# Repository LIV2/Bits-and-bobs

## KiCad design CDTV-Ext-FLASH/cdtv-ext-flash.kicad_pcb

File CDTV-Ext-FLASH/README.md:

# CDTV Extended rom adapter for 39SF010/020/040

## License

[![CC BY-SA 4.0][cc-by-sa-shield]][cc-by-sa]

This work is licensed under a
[Creative Commons Attribution-ShareAlike 4.0 International License][cc-by-sa].

[![CC BY-SA 4.0][cc-by-sa-image]][cc-by-sa]

[cc-by-sa]: http://creativecommons.org/licenses/by-sa/4.0/
[cc-by-sa-image]: https://licensebuttons.net/l/by-sa/4.0/88x31.png
[cc-by-sa-shield]: https://img.shields.io/badge/License-CC%20BY--SA%204.0-lightgrey.svg

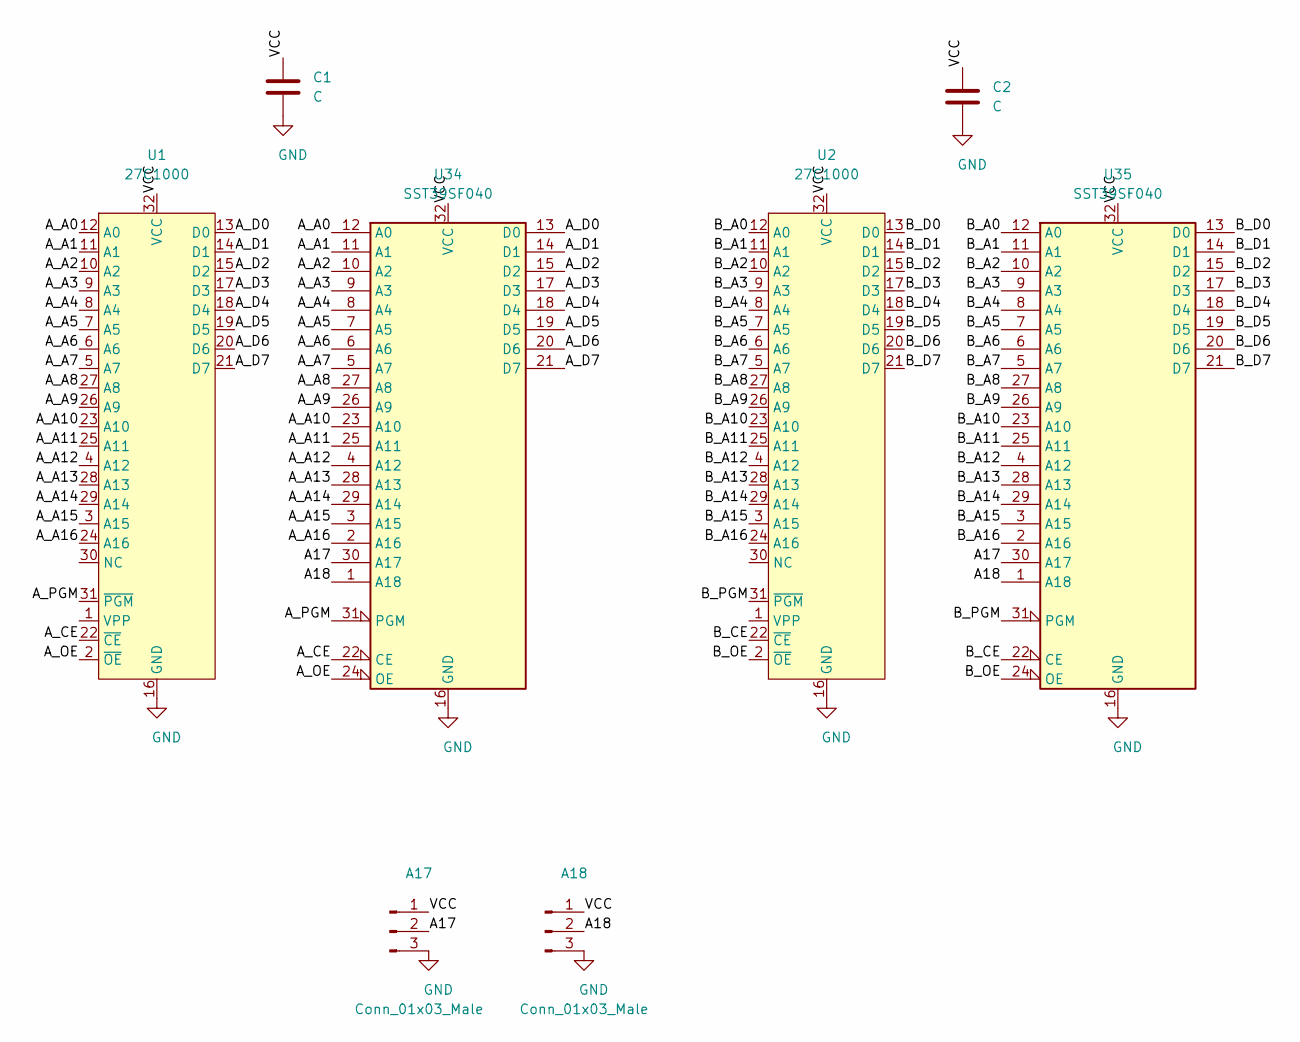
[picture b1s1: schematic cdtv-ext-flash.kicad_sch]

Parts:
A17, A18: Conn_01x03_Male; PinHeader_1x03_P2.54mm_Vertical
C1, C2: C; C_0805_2012Metric_Pad1.18x1.45mm_HandSolder
U1, U2: 27C1000; DIP-32_W15.24mm
U34, U35: SST39SF040; DIP-32_W15.24mm_Socket

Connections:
/A17: A17.2, U34.30 (A17), U35.30 (A17)
/A18: A18.2, U34.1 (A18), U35.1 (A18)
/A_A0: U1.12 (A0), U34.12 (A0)
/A_A1: U1.11 (A1), U34.11 (A1)
/A_A2: U1.10 (A2), U34.10 (A2)
/A_A3: U1.9 (A3), U34.9 (A3)
/A_A4: U1.8 (A4), U34.8 (A4)
/A_A5: U1.7 (A5), U34.7 (A5)
/A_A6: U1.6 (A6), U34.6 (A6)
/A_A7: U1.5 (A7), U34.5 (A7)
/A_A8: U1.27 (A8), U34.27 (A8)
/A_A9: U1.26 (A9), U34.26 (A9)
/A_A10: U1.23 (A10), U34.23 (A10)
/A_A11: U1.25 (A11), U34.25 (A11)
/A_A12: U1.4 (A12), U34.4 (A12)
/A_A13: U1.28 (A13), U34.28 (A13)
/A_A14: U1.29 (A14), U34.29 (A14)
/A_A15: U1.3 (A15), U34.3 (A15)
/A_A16: U1.24 (A16), U34.2 (A16)
/A_CE: U1.22 (~CE), U34.22 (CE)
/A_D0: U1.13 (D0), U34.13 (D0)
/A_D1: U1.14 (D1), U34.14 (D1)
/A_D2: U1.15 (D2), U34.15 (D2)
/A_D3: U1.17 (D3), U34.17 (D3)
/A_D4: U1.18 (D4), U34.18 (D4)
/A_D5: U1.19 (D5), U34.19 (D5)
/A_D6: U1.20 (D6), U34.20 (D6)
/A_D7: U1.21 (D7), U34.21 (D7)
/A_OE: U1.2 (~OE), U34.24 (OE)
/A_PGM: U1.31 (~PGM), U34.31 (PGM)
/B_A0: U2.12 (A0), U35.12 (A0)
/B_A1: U2.11 (A1), U35.11 (A1)
/B_A2: U2.10 (A2), U35.10 (A2)
/B_A3: U2.9 (A3), U35.9 (A3)
/B_A4: U2.8 (A4), U35.8 (A4)
/B_A5: U2.7 (A5), U35.7 (A5)
/B_A6: U2.6 (A6), U35.6 (A6)
/B_A7: U2.5 (A7), U35.5 (A7)
/B_A8: U2.27 (A8), U35.27 (A8)
/B_A9: U2.26 (A9), U35.26 (A9)
/B_A10: U2.23 (A10), U35.23 (A10)
/B_A11: U2.25 (A11), U35.25 (A11)
/B_A12: U2.4 (A12), U35.4 (A12)
/B_A13: U2.28 (A13), U35.28 (A13)
/B_A14: U2.29 (A14), U35.29 (A14)
/B_A15: U2.3 (A15), U35.3 (A15)
/B_A16: U2.24 (A16), U35.2 (A16)
/B_CE: U2.22 (~CE), U35.22 (CE)
/B_D0: U2.13 (D0), U35.13 (D0)
/B_D1: U2.14 (D1), U35.14 (D1)
/B_D2: U2.15 (D2), U35.15 (D2)
/B_D3: U2.17 (D3), U35.17 (D3)
/B_D4: U2.18 (D4), U35.18 (D4)
/B_D5: U2.19 (D5), U35.19 (D5)
/B_D6: U2.20 (D6), U35.20 (D6)
/B_D7: U2.21 (D7), U35.21 (D7)
/B_OE: U2.2 (~OE), U35.24 (OE)
/B_PGM: U2.31 (~PGM), U35.31 (PGM)
/VCC: A17.1, A18.1, C1.1, C2.1, U1.32 (VCC), U2.32 (VCC), U34.32 (VCC), U35.32 (VCC)
GND: A17.3, A18.3, C1.2, C2.2, U1.16 (GND), U2.16 (GND), U34.16 (GND), U35.16 (GND)

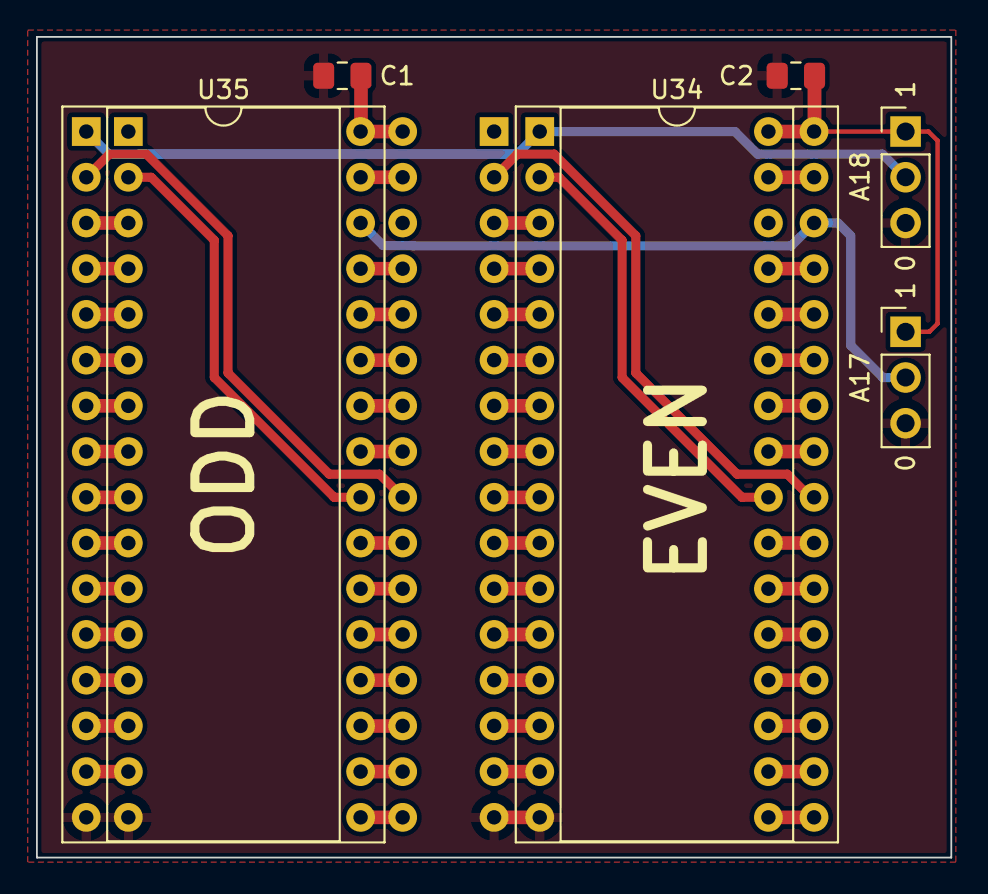
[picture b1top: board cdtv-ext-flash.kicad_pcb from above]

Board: 2 copper layers, 50.8 x 45.6 mm, 8 parts (0 on the bottom side), 60 nets.

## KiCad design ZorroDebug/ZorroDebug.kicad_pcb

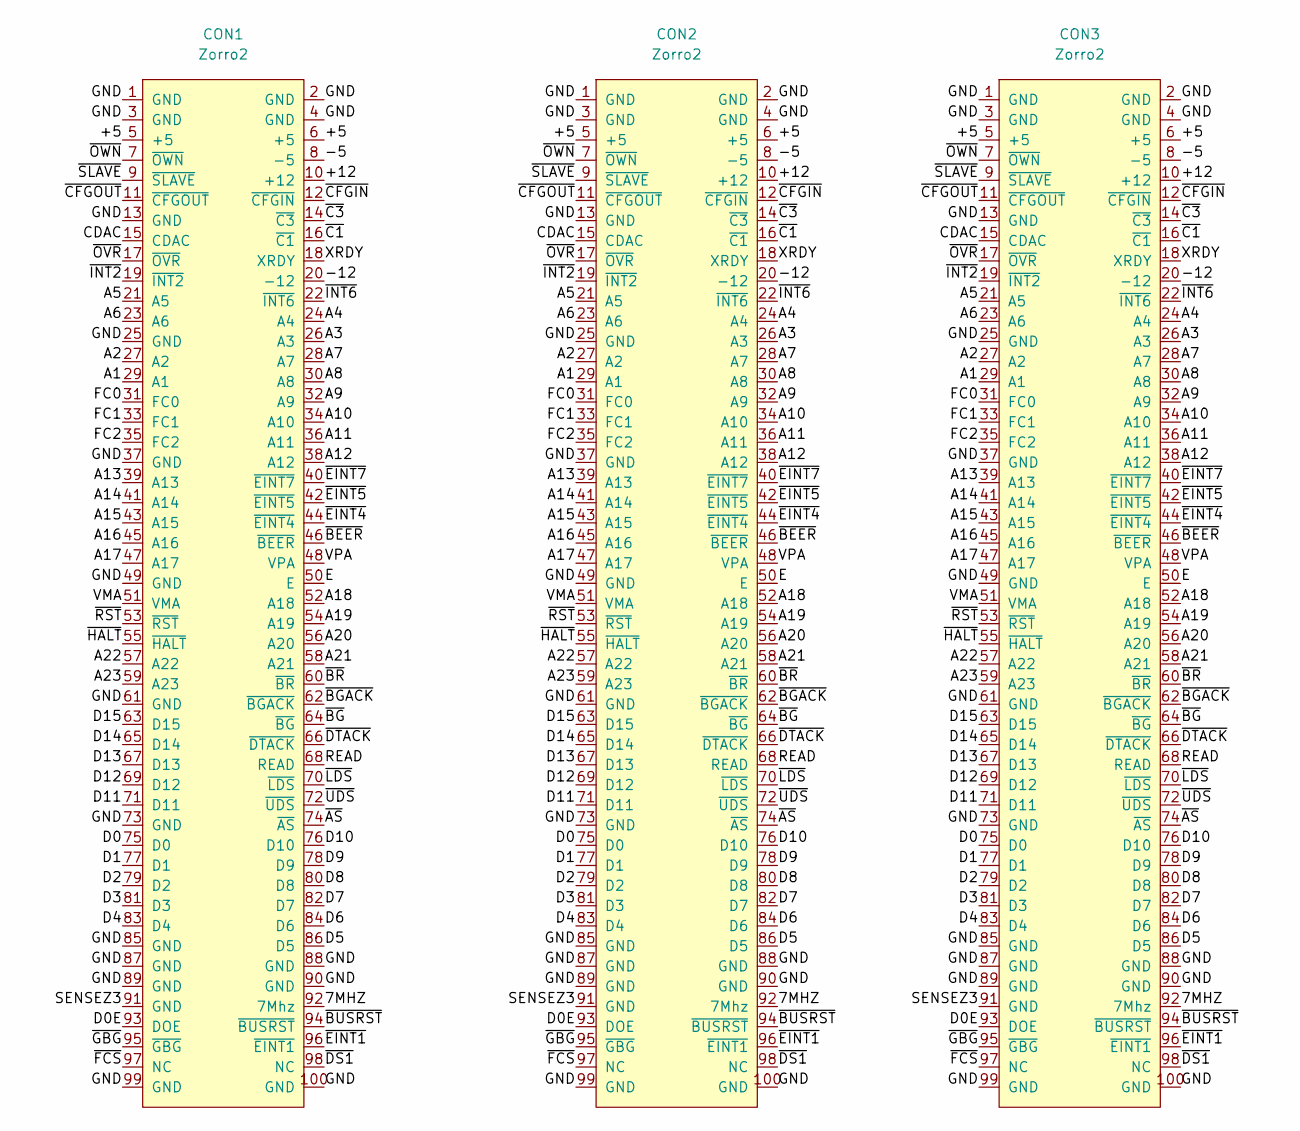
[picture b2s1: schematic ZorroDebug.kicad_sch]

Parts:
CON1: Zorro2; Zorro2-CardEdge
CON2: Zorro2; Zorro2-Connector-Edgemount
CON3: Zorro2; Zorro2-Connector

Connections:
/7MHZ: CON1.92 (7Mhz), CON2.92 (7Mhz), CON3.92 (7Mhz)
/+5: CON1.5 (+5), CON1.6 (+5), CON2.5 (+5), CON2.6 (+5), CON3.5 (+5), CON3.6 (+5)
/+12: CON1.10 (+12), CON2.10 (+12), CON3.10 (+12)
/-5: CON1.8 (-5), CON2.8 (-5), CON3.8 (-5)
/-12: CON1.20 (-12), CON2.20 (-12), CON3.20 (-12)
/A1: CON1.29 (A1), CON2.29 (A1), CON3.29 (A1)
/A2: CON1.27 (A2), CON2.27 (A2), CON3.27 (A2)
/A3: CON1.26 (A3), CON2.26 (A3), CON3.26 (A3)
/A4: CON1.24 (A4), CON2.24 (A4), CON3.24 (A4)
/A5: CON1.21 (A5), CON2.21 (A5), CON3.21 (A5)
/A6: CON1.23 (A6), CON2.23 (A6), CON3.23 (A6)
/A7: CON1.28 (A7), CON2.28 (A7), CON3.28 (A7)
/A8: CON1.30 (A8), CON2.30 (A8), CON3.30 (A8)
/A9: CON1.32 (A9), CON2.32 (A9), CON3.32 (A9)
/A10: CON1.34 (A10), CON2.34 (A10), CON3.34 (A10)
/A11: CON1.36 (A11), CON2.36 (A11), CON3.36 (A11)
/A12: CON1.38 (A12), CON2.38 (A12), CON3.38 (A12)
/A13: CON1.39 (A13), CON2.39 (A13), CON3.39 (A13)
/A14: CON1.41 (A14), CON2.41 (A14), CON3.41 (A14)
/A15: CON1.43 (A15), CON2.43 (A15), CON3.43 (A15)
/A16: CON1.45 (A16), CON2.45 (A16), CON3.45 (A16)
/A17: CON1.47 (A17), CON2.47 (A17), CON3.47 (A17)
/A18: CON1.52 (A18), CON2.52 (A18), CON3.52 (A18)
/A19: CON1.54 (A19), CON2.54 (A19), CON3.54 (A19)
/A20: CON1.56 (A20), CON2.56 (A20), CON3.56 (A20)
/A21: CON1.58 (A21), CON2.58 (A21), CON3.58 (A21)
/A22: CON1.57 (A22), CON2.57 (A22), CON3.57 (A22)
/A23: CON1.59 (A23), CON2.59 (A23), CON3.59 (A23)
/CDAC: CON1.15 (CDAC), CON2.15 (CDAC), CON3.15 (CDAC)
/D0: CON1.75 (D0), CON2.75 (D0), CON3.75 (D0)
/D0E: CON1.93 (DOE), CON2.93 (DOE), CON3.93 (DOE)
/D1: CON1.77 (D1), CON2.77 (D1), CON3.77 (D1)
/D2: CON1.79 (D2), CON2.79 (D2), CON3.79 (D2)
/D3: CON1.81 (D3), CON2.81 (D3), CON3.81 (D3)
/D4: CON1.83 (D4), CON2.83 (D4), CON3.83 (D4)
/D5: CON1.86 (D5), CON2.86 (D5), CON3.86 (D5)
/D6: CON1.84 (D6), CON2.84 (D6), CON3.84 (D6)
/D7: CON1.82 (D7), CON2.82 (D7), CON3.82 (D7)
/D8: CON1.80 (D8), CON2.80 (D8), CON3.80 (D8)
/D9: CON1.78 (D9), CON2.78 (D9), CON3.78 (D9)
/D10: CON1.76 (D10), CON2.76 (D10), CON3.76 (D10)
/D11: CON1.71 (D11), CON2.71 (D11), CON3.71 (D11)
/D12: CON1.69 (D12), CON2.69 (D12), CON3.69 (D12)
/D13: CON1.67 (D13), CON2.67 (D13), CON3.67 (D13)
/D14: CON1.65 (D14), CON2.65 (D14), CON3.65 (D14)
/D15: CON1.63 (D15), CON2.63 (D15), CON3.63 (D15)
/E: CON1.50 (E), CON2.50 (E), CON3.50 (E)
/FC0: CON1.31 (FC0), CON2.31 (FC0), CON3.31 (FC0)
/FC1: CON1.33 (FC1), CON2.33 (FC1), CON3.33 (FC1)
/FC2: CON1.35 (FC2), CON2.35 (FC2), CON3.35 (FC2)
/GND: CON1.1 (GND), CON1.2 (GND), CON1.3 (GND), CON1.4 (GND), CON1.13 (GND), CON1.25 (GND), CON1.37 (GND), CON1.49 (GND), CON1.61 (GND), CON1.73 (GND), CON1.85 (GND), CON1.87 (GND), CON1.88 (GND), CON1.89 (GND), CON1.90 (GND), CON1.99 (GND), CON1.100 (GND), CON2.1 (GND), CON2.2 (GND), CON2.3 (GND), CON2.4 (GND), CON2.13 (GND), CON2.25 (GND), CON2.37 (GND), CON2.49 (GND), CON2.61 (GND), CON2.73 (GND), CON2.85 (GND), CON2.87 (GND), CON2.88 (GND), CON2.89 (GND), CON2.90 (GND), CON2.99 (GND), CON2.100 (GND), CON3.1 (GND), CON3.2 (GND), CON3.3 (GND), CON3.4 (GND), CON3.13 (GND), CON3.25 (GND), CON3.37 (GND), CON3.49 (GND), CON3.61 (GND), CON3.73 (GND), CON3.85 (GND), CON3.87 (GND), CON3.88 (GND), CON3.89 (GND), CON3.90 (GND), CON3.99 (GND), CON3.100 (GND)
/READ: CON1.68 (READ), CON2.68 (READ), CON3.68 (READ)
/SENSEZ3: CON1.91 (GND), CON2.91 (GND), CON3.91 (GND)
/VMA: CON1.51 (VMA), CON2.51 (VMA), CON3.51 (VMA)
/VPA: CON1.48 (VPA), CON2.48 (VPA), CON3.48 (VPA)
/XRDY: CON1.18 (XRDY), CON2.18 (XRDY), CON3.18 (XRDY)
/~AS: CON1.74 (~AS), CON2.74 (~AS), CON3.74 (~AS)
/~BEER: CON1.46 (~BEER), CON2.46 (~BEER), CON3.46 (~BEER)
/~BGACK: CON1.62 (~BGACK), CON2.62 (~BGACK), CON3.62 (~BGACK)
/~BG: CON1.64 (~BG), CON2.64 (~BG), CON3.64 (~BG)
/~BR: CON1.60 (~BR), CON2.60 (~BR), CON3.60 (~BR)
/~BUSRST: CON1.94 (~BUSRST), CON2.94 (~BUSRST), CON3.94 (~BUSRST)
/~C1: CON1.16 (~C1), CON2.16 (~C1), CON3.16 (~C1)
/~C3: CON1.14 (~C3), CON2.14 (~C3), CON3.14 (~C3)
/~CFGIN: CON1.12 (~CFGIN), CON2.12 (~CFGIN), CON3.12 (~CFGIN)
/~CFGOUT: CON1.11 (~CFGOUT), CON2.11 (~CFGOUT), CON3.11 (~CFGOUT)
/~DS1: CON1.98 (NC), CON2.98 (NC), CON3.98 (NC)
/~DTACK: CON1.66 (~DTACK), CON2.66 (~DTACK), CON3.66 (~DTACK)
/~EINT1: CON1.96 (~EINT1), CON2.96 (~EINT1), CON3.96 (~EINT1)
/~EINT4: CON1.44 (~EINT4), CON2.44 (~EINT4), CON3.44 (~EINT4)
/~EINT5: CON1.42 (~EINT5), CON2.42 (~EINT5), CON3.42 (~EINT5)
/~EINT7: CON1.40 (~EINT7), CON2.40 (~EINT7), CON3.40 (~EINT7)
/~FCS: CON1.97 (NC), CON2.97 (NC), CON3.97 (NC)
/~GBG: CON1.95 (~GBG), CON2.95 (~GBG), CON3.95 (~GBG)
/~HALT: CON1.55 (~HALT), CON2.55 (~HALT), CON3.55 (~HALT)
/~INT2: CON1.19 (~INT2), CON2.19 (~INT2), CON3.19 (~INT2)
/~INT6: CON1.22 (~INT6), CON2.22 (~INT6), CON3.22 (~INT6)
/~LDS: CON1.70 (~LDS), CON2.70 (~LDS), CON3.70 (~LDS)
/~OVR: CON1.17 (~OVR), CON2.17 (~OVR), CON3.17 (~OVR)
/~OWN: CON1.7 (~OWN), CON2.7 (~OWN), CON3.7 (~OWN)
/~RST: CON1.53 (~RST), CON2.53 (~RST), CON3.53 (~RST)
/~SLAVE: CON1.9 (~SLAVE), CON2.9 (~SLAVE), CON3.9 (~SLAVE)
/~UDS: CON1.72 (~UDS), CON2.72 (~UDS), CON3.72 (~UDS)

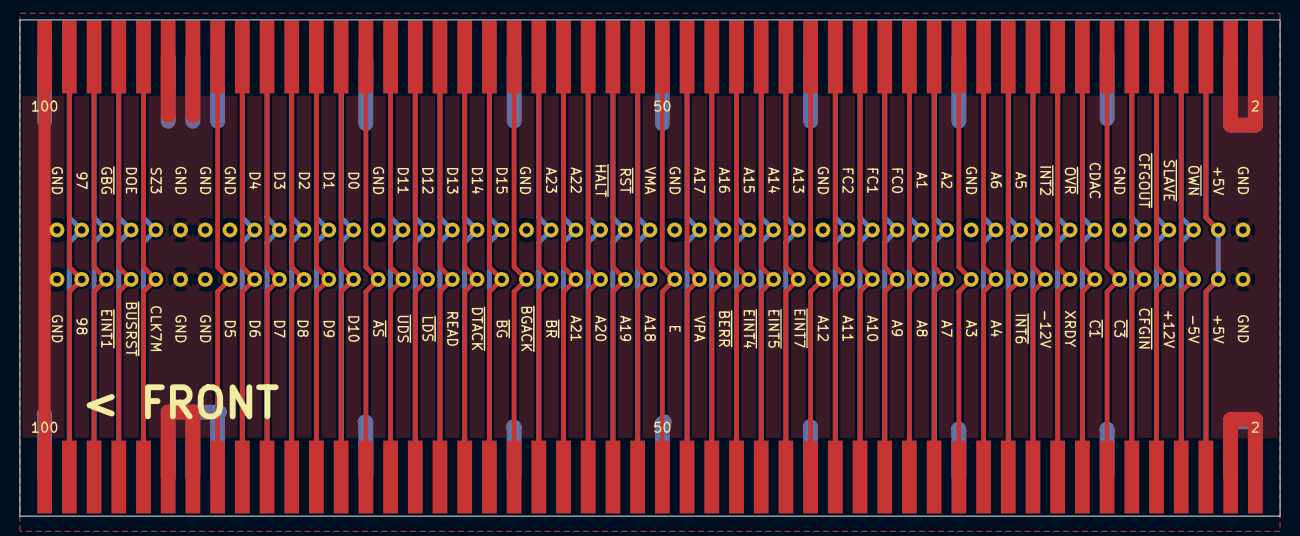
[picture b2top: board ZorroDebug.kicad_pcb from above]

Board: 2 copper layers, 129.5 x 51.0 mm, 3 parts (0 on the bottom side), 83 nets.

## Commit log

2022-04-24 Initial commit, add Zorro debug board
2022-11-19 Add CDTV-Extended-Flash
2025-01-06 Add BootSelectWB
2025-01-06 Update main.c for some typos and handling 6 KS variants
2025-01-18 Fixups to make it compile
2025-01-18 Fixup Kick version check
    SysBase->SoftVer contains the revision not the major release
